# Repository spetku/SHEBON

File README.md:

# open_SHEBON
a platform for sensing and indicating bio-data!

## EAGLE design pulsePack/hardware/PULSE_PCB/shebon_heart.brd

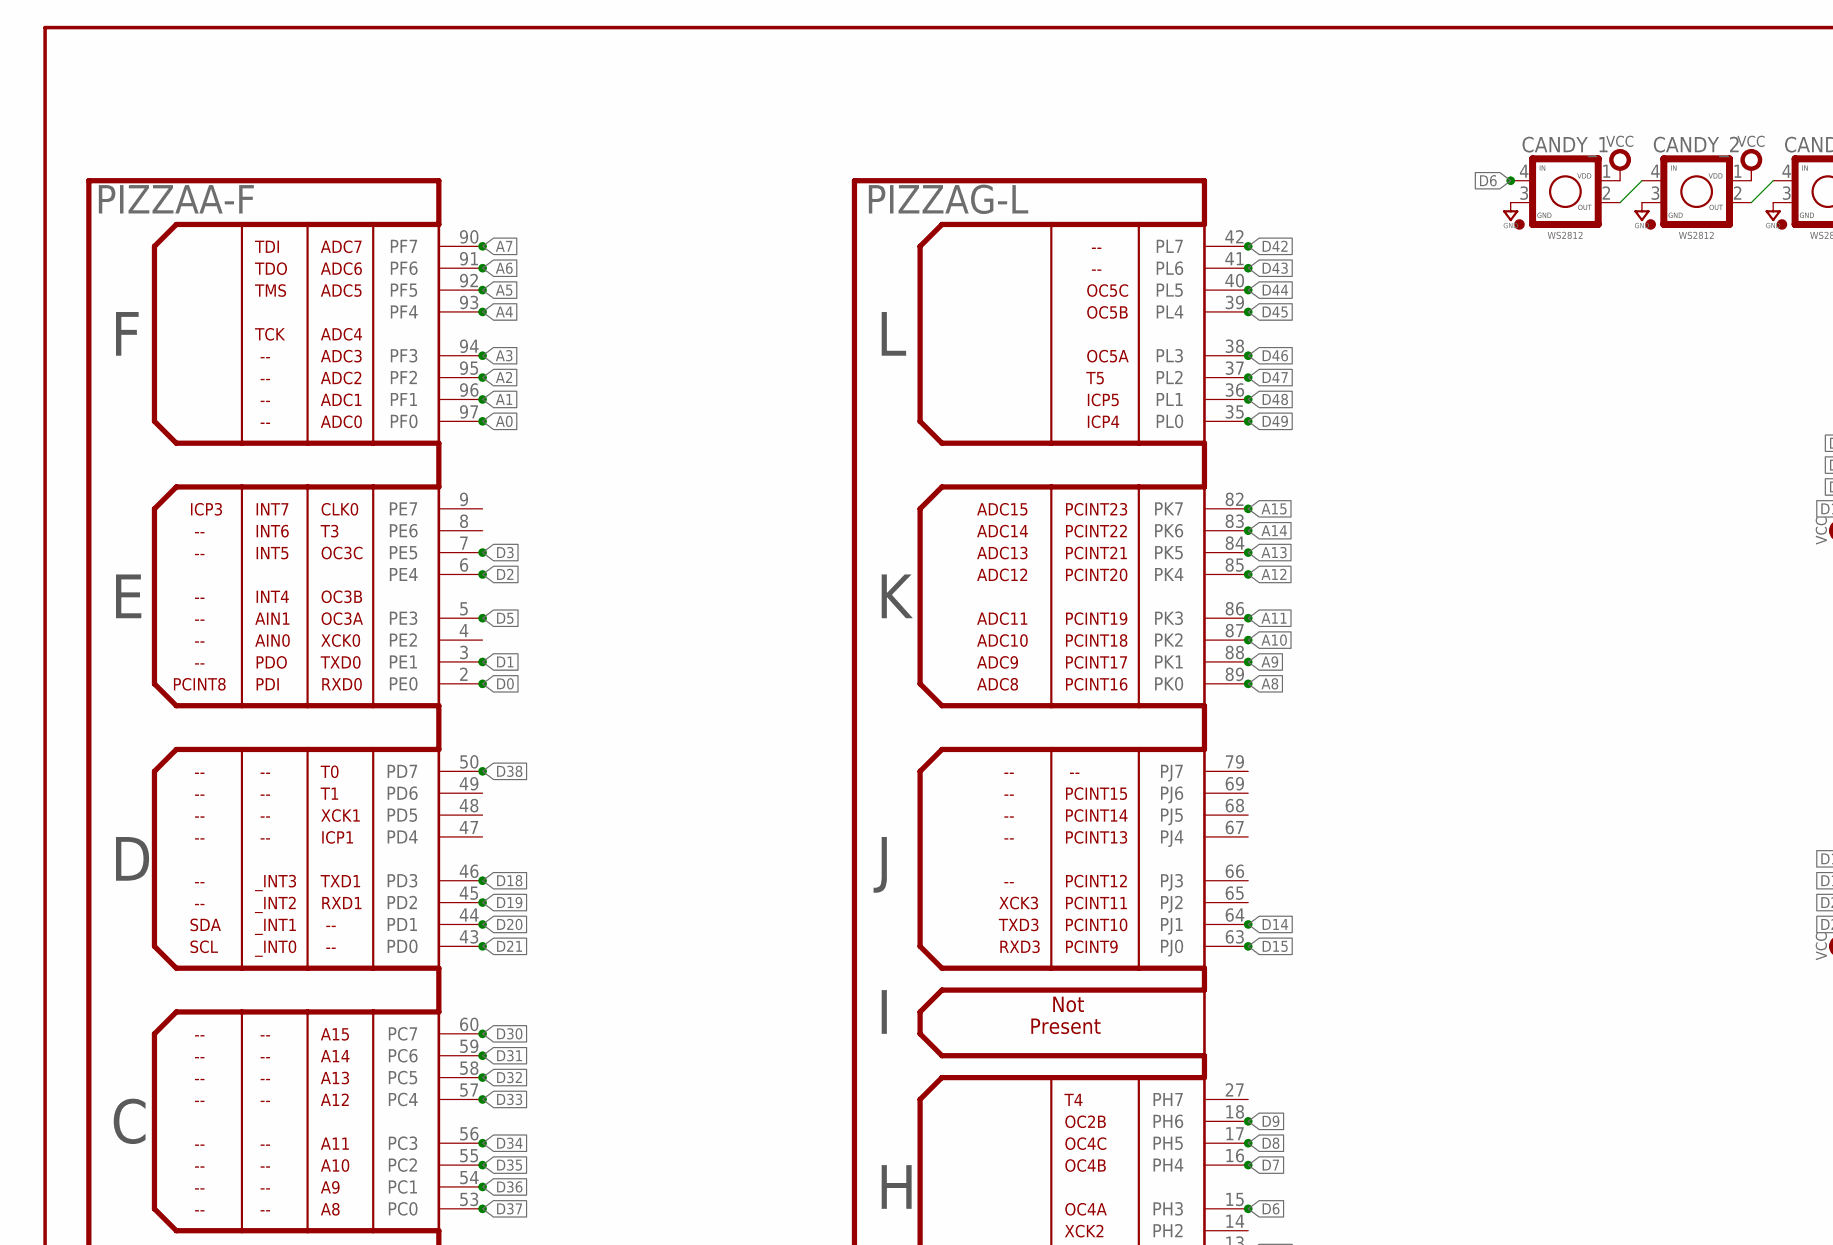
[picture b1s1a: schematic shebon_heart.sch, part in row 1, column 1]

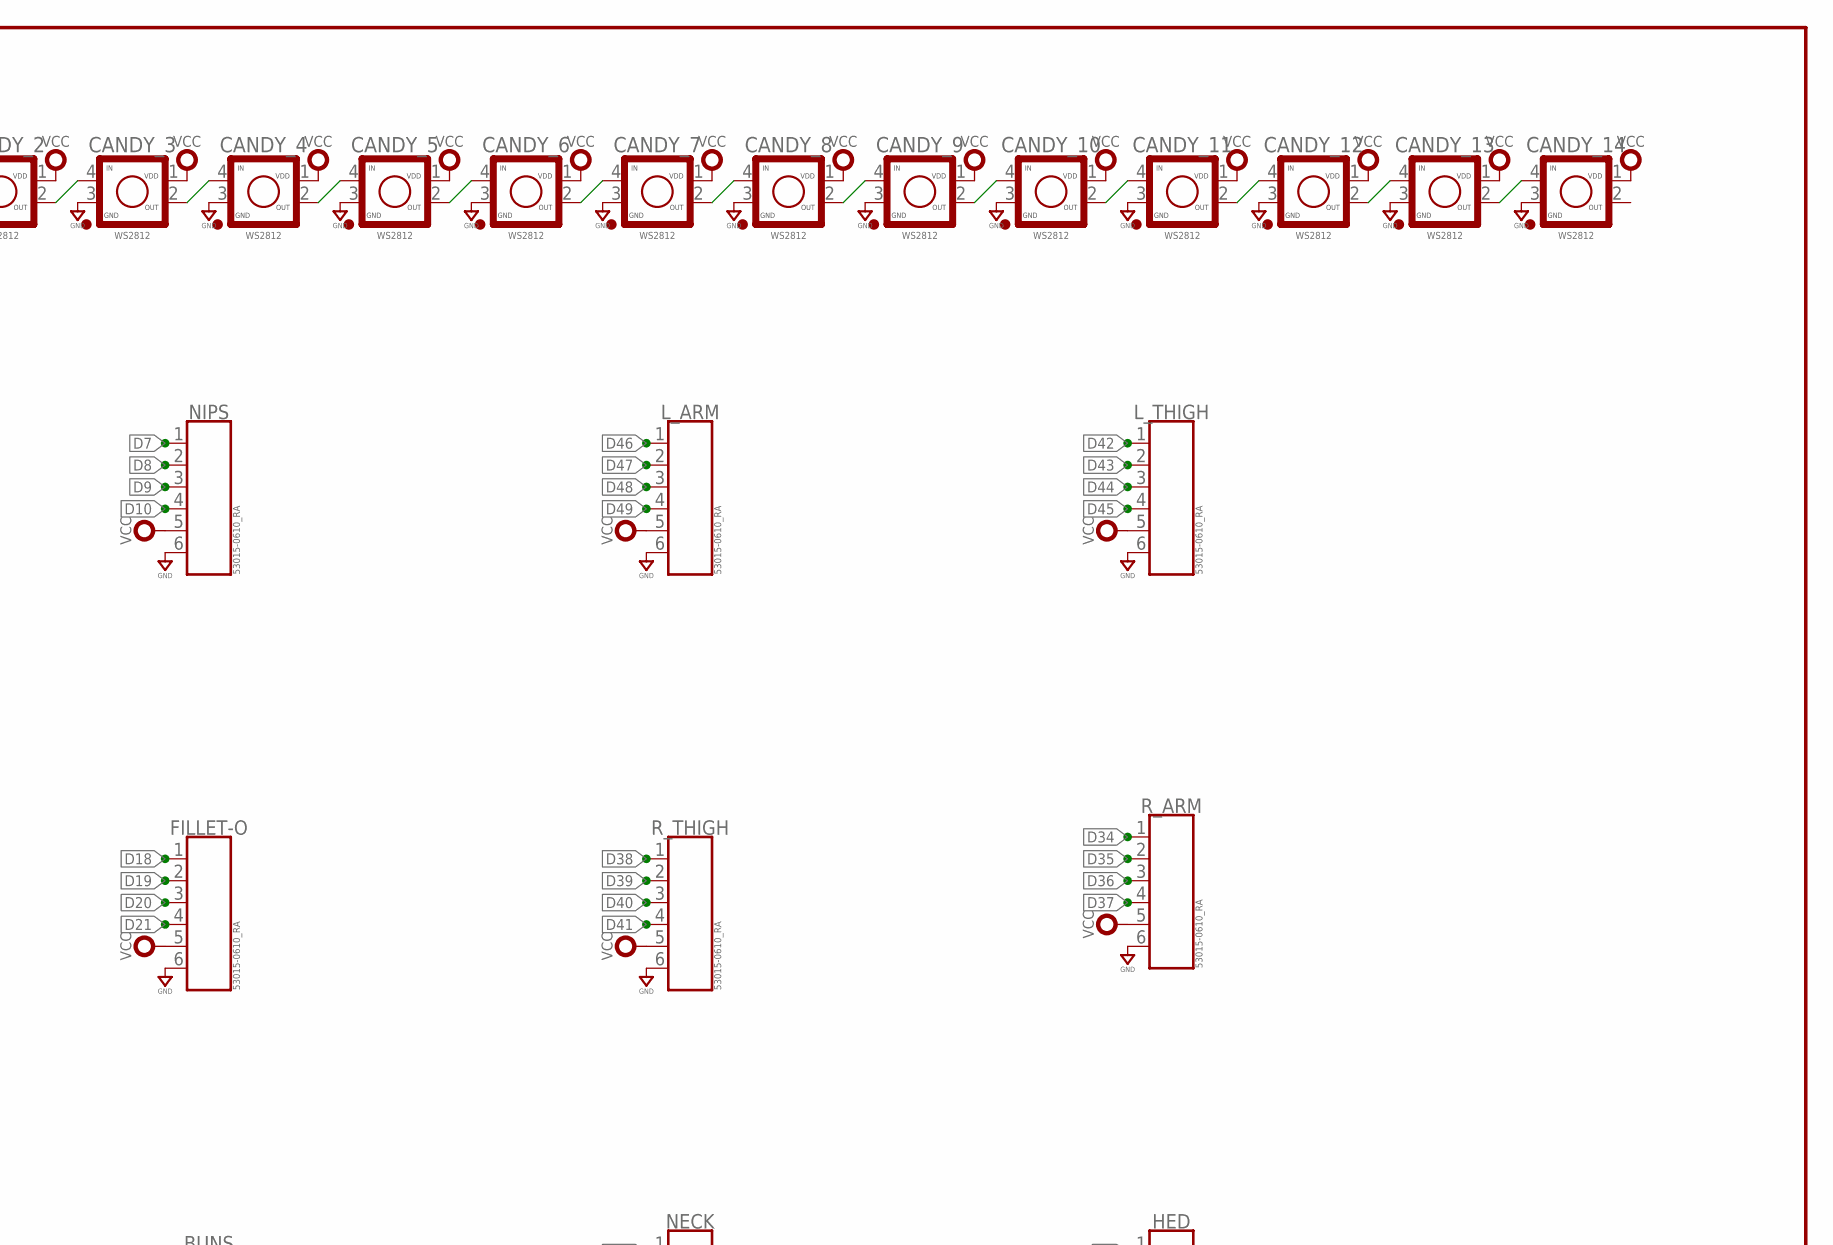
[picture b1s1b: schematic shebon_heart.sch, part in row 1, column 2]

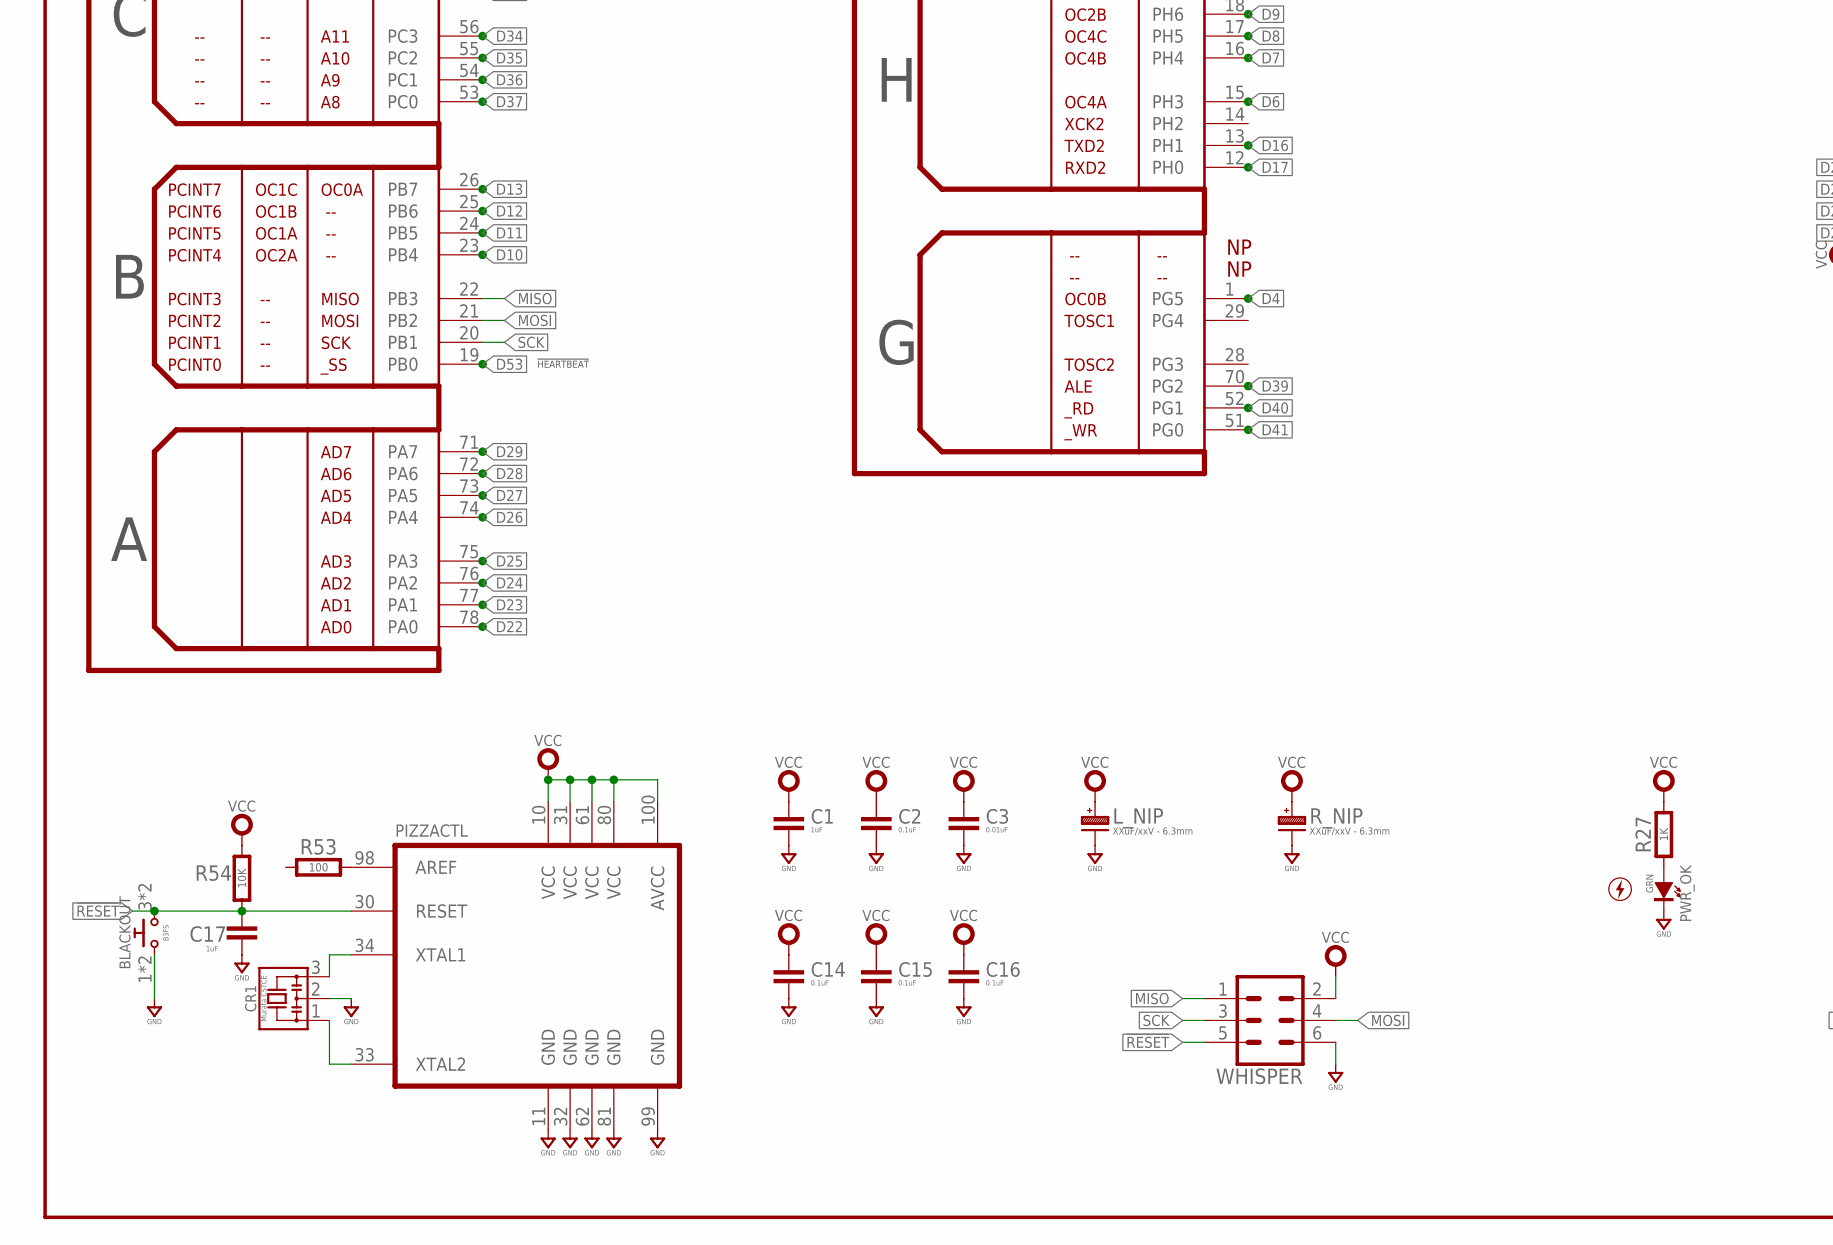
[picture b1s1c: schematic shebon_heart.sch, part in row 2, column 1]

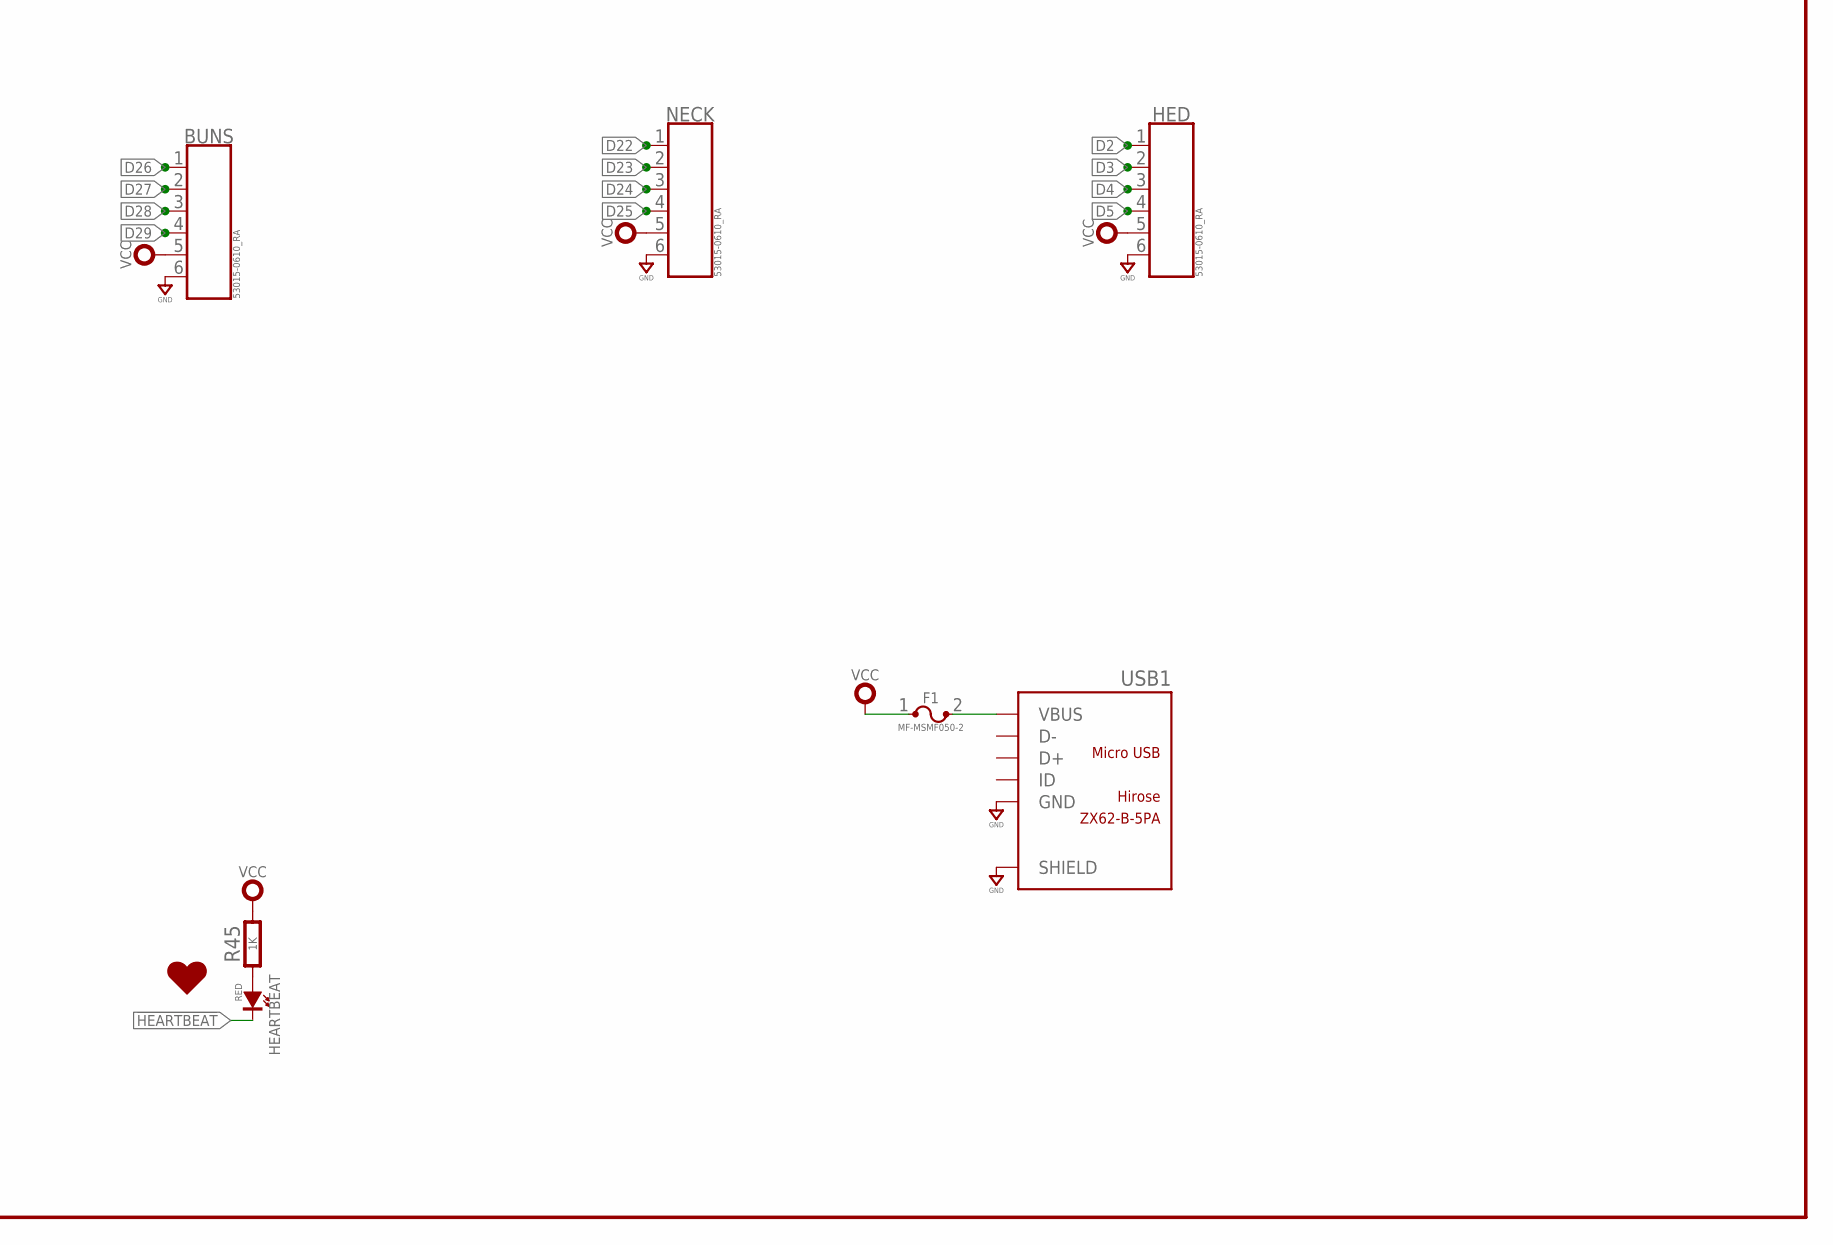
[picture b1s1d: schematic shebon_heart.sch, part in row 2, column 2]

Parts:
BLACKOUT: B3FS
BUNS: 53015-0610_RA; MICROBLADE-RA-06P
C1, C17: 1uF; 0603
C2, C14, C15, C16: 0.1uF; 0603
C3: 0.01uF; 0603
CANDY_1, CANDY_2, CANDY_3, CANDY_4, CANDY_5, CANDY_6, CANDY_7, CANDY_8, CANDY_9, CANDY_10, CANDY_11, CANDY_12, CANDY_13, CANDY_14: WS2812; NEOPIXEL
CR1: Murata CSTCE; MURATA_CSTCE
F1: MF-MSMF050-2; BOURNS-MF-MSMF
FILLET-O: 53015-0610_RA; MICROBLADE-RA-06P
HEARTBEAT: RED; SMD_0603
HED: 53015-0610_RA; MICROBLADE-RA-06P
L_ARM: 53015-0610_RA; MICROBLADE-RA-06P
L_NIP: XXuF/xxV - 6.3mm; CAP_ALUM_SMT_6.3
L_THIGH: 53015-0610_RA; MICROBLADE-RA-06P
NECK: 53015-0610_RA; MICROBLADE-RA-06P
NIPS: 53015-0610_RA; MICROBLADE-RA-06P
PIZZA: ATMEGA-2560; TQFP-100-A
PWR_OK: GRN; SMD_0603
R27, R45: 1K; 0603
R53: 100; 0603
R54: 10K; 0603
R_ARM: 53015-0610_RA; MICROBLADE-RA-06P
R_NIP: XXuF/xxV - 6.3mm; CAP_ALUM_SMT_6.3
R_THIGH: 53015-0610_RA; MICROBLADE-RA-06P
U$2: ELECTRICITY-050X050MM; ELECTRICITY-GLYPH-05X05MM
U$3: HEART-05X04MM; HEART-GLYPH-05X04MM
USB1: ZX62-B-5PA; MICRO-USB5+6P-SMD-0.65-AB
WHISPER: MA03-2

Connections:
!HEARTBEAT: HEARTBEAT.K (C)
!RESET: BLACKOUT.3 (2), BLACKOUT.4 (2), C17.1, PIZZA.30 (RESET), R54.2, WHISPER.5
A0: PIZZA.97 (PF0)
A1: PIZZA.96 (PF1)
A2: PIZZA.95 (PF2)
A3: PIZZA.94 (PF3)
A4: PIZZA.93 (PF4)
A5: PIZZA.92 (PF5)
A6: PIZZA.91 (PF6)
A7: PIZZA.90 (PF7)
A8: PIZZA.89 (PK0)
A9: PIZZA.88 (PK1)
A10: PIZZA.87 (PK2)
A11: PIZZA.86 (PK3)
A12: PIZZA.85 (PK4)
A13: PIZZA.84 (PK5)
A14: PIZZA.83 (PK6)
A15: PIZZA.82 (PK7)
D0: PIZZA.2 (PE0)
D1: PIZZA.3 (PE1)
D2: HED.1, PIZZA.6 (PE4)
D3: HED.2, PIZZA.7 (PE5)
D4: HED.3, PIZZA.1 (PG5)
D5: HED.4, PIZZA.5 (PE3)
D6: CANDY_1.4 (OUT), PIZZA.15 (PH3)
D7: NIPS.1, PIZZA.16 (PH4)
D8: NIPS.2, PIZZA.17 (PH5)
D9: NIPS.3, PIZZA.18 (PH6)
D10: NIPS.4, PIZZA.23 (PB4)
D11: PIZZA.24 (PB5)
D12: PIZZA.25 (PB6)
D13: PIZZA.26 (PB7)
D14: PIZZA.64 (PJ1)
D15: PIZZA.63 (PJ0)
D16: PIZZA.13 (PH1)
D17: PIZZA.12 (PH0)
D18: FILLET-O.1, PIZZA.46 (PD3)
D19: FILLET-O.2, PIZZA.45 (PD2)
D20: FILLET-O.3, PIZZA.44 (PD1)
D21: FILLET-O.4, PIZZA.43 (PD0)
D22: NECK.1, PIZZA.78 (PA0)
D23: NECK.2, PIZZA.77 (PA1)
D24: NECK.3, PIZZA.76 (PA2)
D25: NECK.4, PIZZA.75 (PA3)
D26: BUNS.1, PIZZA.74 (PA4)
D27: BUNS.2, PIZZA.73 (PA5)
D28: BUNS.3, PIZZA.72 (PA6)
D29: BUNS.4, PIZZA.71 (PA7)
D30: PIZZA.60 (PC7)
D31: PIZZA.59 (PC6)
D32: PIZZA.58 (PC5)
D33: PIZZA.57 (PC4)
D34: PIZZA.56 (PC3), R_ARM.1
D35: PIZZA.55 (PC2), R_ARM.2
D36: PIZZA.54 (PC1), R_ARM.3
D37: PIZZA.53 (PC0), R_ARM.4
D38: PIZZA.50 (PD7), R_THIGH.1
D39: PIZZA.70 (PG2), R_THIGH.2
D40: PIZZA.52 (PG1), R_THIGH.3
D41: PIZZA.51 (PG0), R_THIGH.4
D42: L_THIGH.1, PIZZA.42 (PL7)
D43: L_THIGH.2, PIZZA.41 (PL6)
D44: L_THIGH.3, PIZZA.40 (PL5)
D45: L_THIGH.4, PIZZA.39 (PL4)
D46: L_ARM.1, PIZZA.38 (PL3)
D47: L_ARM.2, PIZZA.37 (PL2)
D48: L_ARM.3, PIZZA.36 (PL1)
D49: L_ARM.4, PIZZA.35 (PL0)
D53: PIZZA.19 (PB0)
GND: BLACKOUT.1, BLACKOUT.2 (1), BUNS.6, C1.2, C2.2, C3.2, C14.2, C15.2, C16.2, C17.2, CANDY_1.3 (GND), CANDY_2.3 (GND), CANDY_3.3 (GND), CANDY_4.3 (GND), CANDY_5.3 (GND), CANDY_6.3 (GND), CANDY_7.3 (GND), CANDY_8.3 (GND), CANDY_9.3 (GND), CANDY_10.3 (GND), CANDY_11.3 (GND), CANDY_12.3 (GND), CANDY_13.3 (GND), CANDY_14.3 (GND), CR1.2, FILLET-O.6, HED.6, L_ARM.6, L_NIP.- (N), L_THIGH.6, NECK.6, NIPS.6, PIZZA.11 (GND), PIZZA.32 (GND), PIZZA.62 (GND), PIZZA.81 (GND), PIZZA.99 (GND), PWR_OK.K (C), R_ARM.6, R_NIP.- (N), R_THIGH.6, USB1.5 (GND), USB1.P1 (SHIELD), USB1.P2 (SHIELD), USB1.P3_1 (SHIELD), USB1.P3_2 (SHIELD), USB1.P3_3 (SHIELD), USB1.P4_1 (SHIELD), USB1.P4_2 (SHIELD), USB1.P4_3 (SHIELD), USB1.P5 (SHIELD), USB1.P6 (SHIELD), WHISPER.6
MISO: PIZZA.22 (PB3), WHISPER.1
MOSI: PIZZA.21 (PB2), WHISPER.4
unnamed: CR1.3, PIZZA.34 (XTAL1)
unnamed: CR1.1, PIZZA.33 (XTAL2)
unnamed: CANDY_1.2 (IN), CANDY_2.4 (OUT)
unnamed: CANDY_2.2 (IN), CANDY_3.4 (OUT)
unnamed: CANDY_3.2 (IN), CANDY_4.4 (OUT)
unnamed: CANDY_4.2 (IN), CANDY_5.4 (OUT)
unnamed: CANDY_5.2 (IN), CANDY_6.4 (OUT)
unnamed: CANDY_6.2 (IN), CANDY_7.4 (OUT)
unnamed: CANDY_7.2 (IN), CANDY_8.4 (OUT)
unnamed: CANDY_8.2 (IN), CANDY_9.4 (OUT)
unnamed: CANDY_9.2 (IN), CANDY_10.4 (OUT)
unnamed: CANDY_10.2 (IN), CANDY_11.4 (OUT)
unnamed: CANDY_11.2 (IN), CANDY_12.4 (OUT)
unnamed: CANDY_12.2 (IN), CANDY_13.4 (OUT)
unnamed: CANDY_13.2 (IN), CANDY_14.4 (OUT)
unnamed: PWR_OK.A, R27.1
unnamed: HEARTBEAT.A, R45.1
unnamed: PIZZA.98 (AREF), R53.2
SCK: PIZZA.20 (PB1), WHISPER.3
VBUS: F1.2, USB1.1 (VBUS)
VCC: BUNS.5, C1.1, C2.1, C3.1, C14.1, C15.1, C16.1, CANDY_1.1 (VDD), CANDY_2.1 (VDD), CANDY_3.1 (VDD), CANDY_4.1 (VDD), CANDY_5.1 (VDD), CANDY_6.1 (VDD), CANDY_7.1 (VDD), CANDY_8.1 (VDD), CANDY_9.1 (VDD), CANDY_10.1 (VDD), CANDY_11.1 (VDD), CANDY_12.1 (VDD), CANDY_13.1 (VDD), CANDY_14.1 (VDD), F1.1, FILLET-O.5, HED.5, L_ARM.5, L_NIP.+, L_THIGH.5, NECK.5, NIPS.5, PIZZA.10 (VCC), PIZZA.31 (VCC), PIZZA.61 (VCC), PIZZA.80 (VCC), PIZZA.100 (AVCC), R27.2, R45.2, R54.1, R_ARM.5, R_NIP.+, R_THIGH.5, WHISPER.2

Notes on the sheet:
!HEARTBEAT

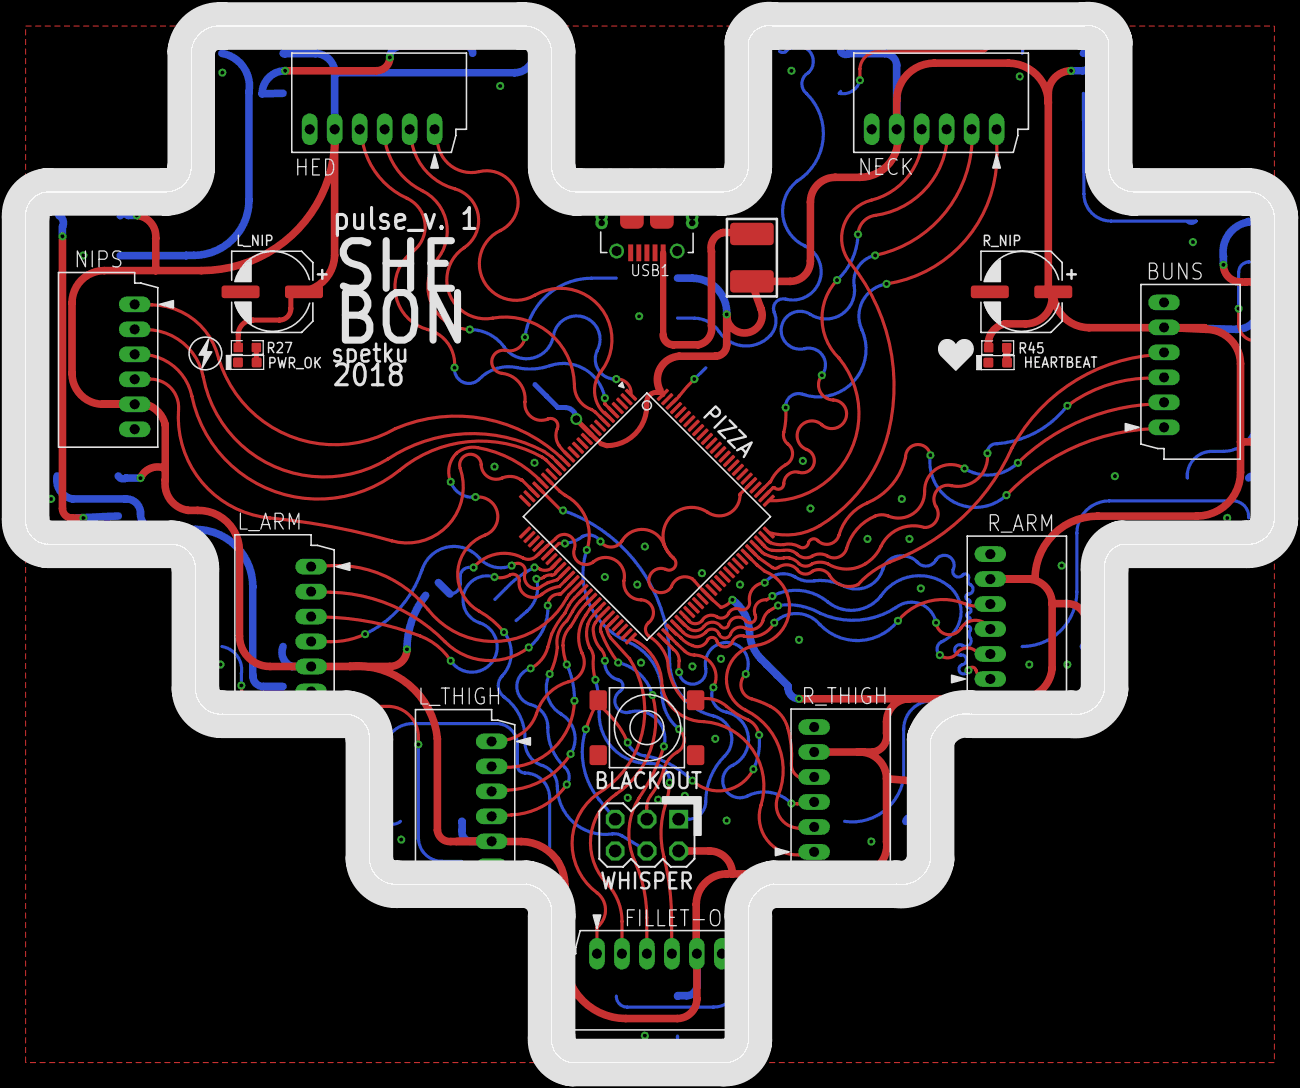
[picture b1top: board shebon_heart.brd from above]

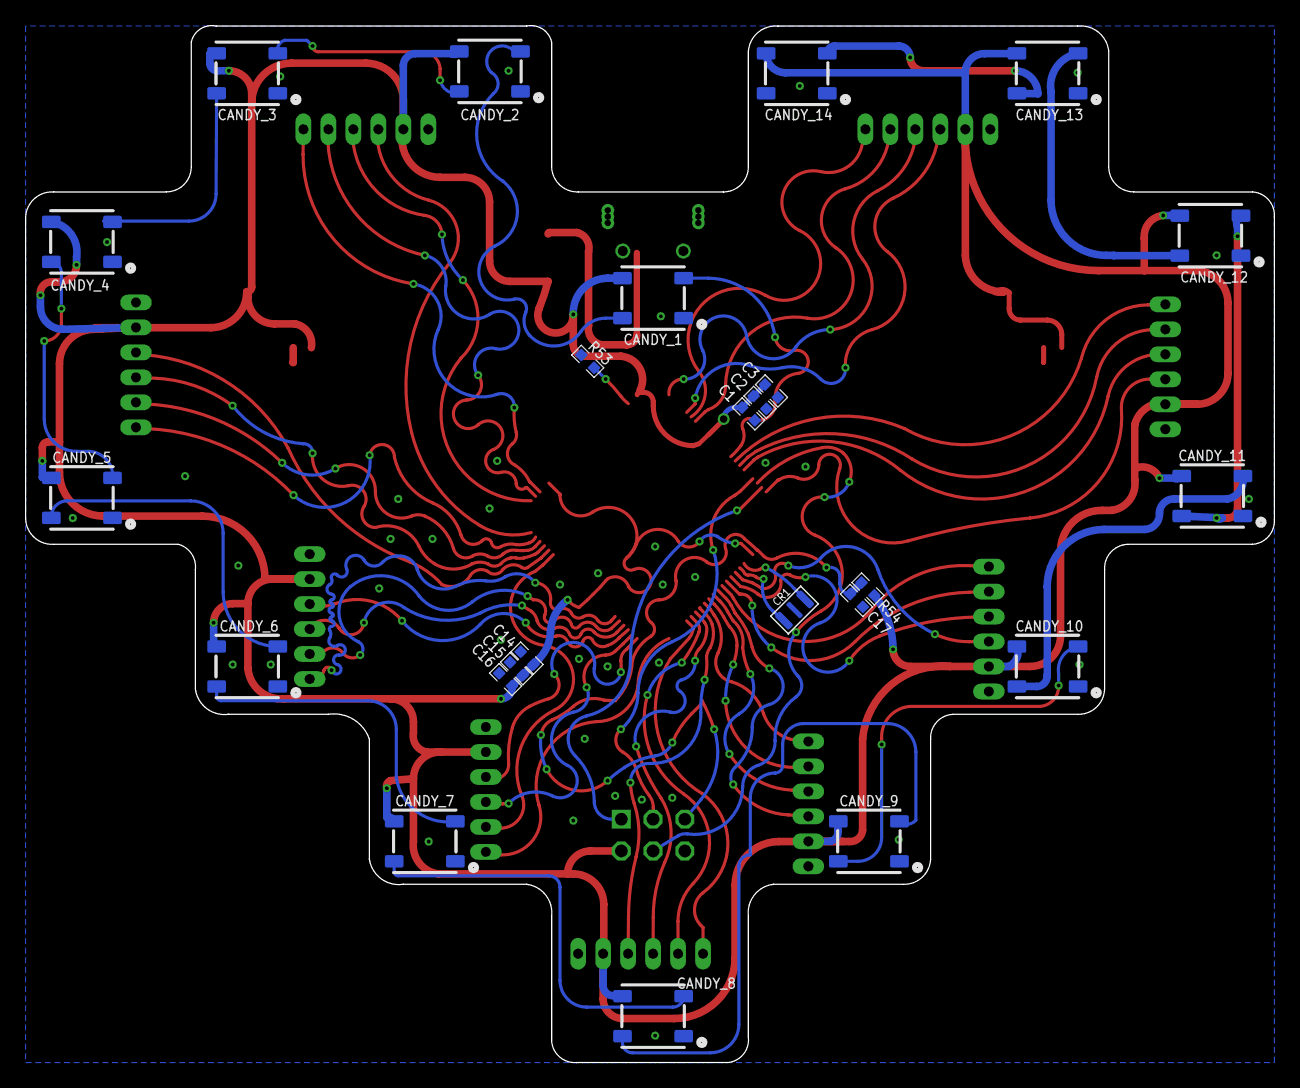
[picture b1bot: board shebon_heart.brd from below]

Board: 2 copper layers, 100.0 x 83.0 mm, 46 parts (24 on the bottom side), 62 nets.

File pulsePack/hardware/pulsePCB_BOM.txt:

SHE BON : PULSE | by SARAH PETKUS

Partlist exported from shebon_heart.sch at 10/21/18 2:06 PM

Part      Value                 Device                     Package                   Description                MPN        VALUE           
PIZZA                           ATMEGA-2560                TQFP-100-A                Atmel ATmega 640/1280/2560                            
BLACKOUT  B3FS                  PUSHBTN-MOMB3FS            B3FS                      Pushbutton Switch                     B3FS                      
C1        1uF                   CAPACITOR0603              0603                      Capacitor  CAP                                        
C2        0.1uF                 CAPACITOR0603              0603                      Capacitor  CAP                                        
C3        0.01uF                CAPACITOR0603              0603                      Capacitor  CAP                                        
C14       0.1uF                 CAPACITOR0603              0603                      Capacitor  CAP                                        
C15       0.1uF                 CAPACITOR0603              0603                      Capacitor  CAP                                        
C16       0.1uF                 CAPACITOR0603              0603                      Capacitor  CAP                                        
C17       1uF                   CAPACITOR0603              0603                      Capacitor  CAP                                        
L_NIP     330uF/6.3V - 6.3mm    CAPACITOR_POL-ALUM-SMT-6.3 CAP_ALUM_SMT_6.3          Polarized Capacitor                   XXuF/xxV - 6.3mm
R_NIP     330uF/6.3V - 6.3mm    CAPACITOR_POL-ALUM-SMT-6.3 CAP_ALUM_SMT_6.3          Polarized Capacitor                   XXuF/xxV - 6.3mm
CANDY_1   WS2812                NEOPPIXEL5X5               NEOPIXEL                  Adafruit NeoPixel                     WS2812          
CANDY_2   WS2812                NEOPPIXEL5X5               NEOPIXEL                  Adafruit NeoPixel                     WS2812          
CANDY_3   WS2812                NEOPPIXEL5X5               NEOPIXEL                  Adafruit NeoPixel                     WS2812          
CANDY_4   WS2812                NEOPPIXEL5X5               NEOPIXEL                  Adafruit NeoPixel                     WS2812          
CANDY_5   WS2812                NEOPPIXEL5X5               NEOPIXEL                  Adafruit NeoPixel                     WS2812          
CANDY_6   WS2812                NEOPPIXEL5X5               NEOPIXEL                  Adafruit NeoPixel                     WS2812          
CANDY_7   WS2812                NEOPPIXEL5X5               NEOPIXEL                  Adafruit NeoPixel                     WS2812          
CANDY_8   WS2812                NEOPPIXEL5X5               NEOPIXEL                  Adafruit NeoPixel                     WS2812          
CANDY_9   WS2812                NEOPPIXEL5X5               NEOPIXEL                  Adafruit NeoPixel                     WS2812          
CANDY_10  WS2812                NEOPPIXEL5X5               NEOPIXEL                  Adafruit NeoPixel                     WS2812          
CANDY_11  WS2812                NEOPPIXEL5X5               NEOPIXEL                  Adafruit NeoPixel                     WS2812          
CANDY_12  WS2812                NEOPPIXEL5X5               NEOPIXEL                  Adafruit NeoPixel                     WS2812          
CANDY_13  WS2812                NEOPPIXEL5X5               NEOPIXEL                  Adafruit NeoPixel                     WS2812          
CANDY_14  WS2812                NEOPPIXEL5X5               NEOPIXEL                  Adafruit NeoPixel                     WS2812          
CR1       Murata CSTCE          RESONATORMURATA-CSTCE      MURATA_CSTCE              resonator xtal                        Murata CSTCE    
F1        MF-MSMF050-2          FUSEBOURNS-MF-MSMF         BOURNS-MF-MSMF            Fuse                                  MF-MSMF050-2    
FILLET-O  53015-0610_RA         53015-0610_RA              MICROBLADE-RA-06P         Molex, Microblade, 6-pin                              
HED       53015-0610_RA         53015-0610_RA              MICROBLADE-RA-06P         Molex, Microblade, 6-pin                              
BUNS      53015-0610_RA         53015-0610_RA              MICROBLADE-RA-06P         Molex, Microblade, 6-pin                    
L_ARM     53015-0610_RA         53015-0610_RA              MICROBLADE-RA-06P         Molex, Microblade, 6-pin                              
L_THIGH   53015-0610_RA         53015-0610_RA              MICROBLADE-RA-06P         Molex, Microblade, 6-pin                              
R_ARM     53015-0610_RA         53015-0610_RA              MICROBLADE-RA-06P         Molex, Microblade, 6-pin                              
R_THIGH   53015-0610_RA         53015-0610_RA              MICROBLADE-RA-06P         Molex, Microblade, 6-pin                                                                                  
NECK      53015-0610_RA         53015-0610_RA              MICROBLADE-RA-06P         Molex, Microblade, 6-pin                              
NIPS      53015-0610_RA         53015-0610_RA              MICROBLADE-RA-06P         Molex, Microblade, 6-pin                              
WHISPER                         MA03-2                     MA03-2                    PIN HEADER                                            
USB1      ZX62-B-5PA            MICRO-USB-SMD(ZX62-B-5PA)  MICRO-USB5+6P-SMD-0.65-AB 320010005                  ZX62-B-5PA ZX62-B-5PA      
PWR_OK    GRN                   SMT0603                    SMD_0603                  LED SMT 0603 0805 1206                                
HEARTBEAT RED                   SMT0603                    SMD_0603                  LED SMT 0603 0805 1206                                
R27       1K                    RESISTOR0603               0603                      Resistor                                              
R45       1K                    RESISTOR0603               0603                      Resistor                                              
R53       100                   RESISTOR0603               0603                      Resistor                                              
R54       10K                   RESISTOR0603               0603                      Resistor

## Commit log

2018-10-20 popGirl v.1 STL files added
    First version of the popGirl enclosure
2018-10-21 Ignore DS_Store files
    Ignore DS_store files
2018-10-21 folder name change
    I reorganized stuff
2018-10-21 No more DS_Store
    Remove all DS_Store files.
2018-10-21 Added Hardware Setup Notes
    Hardware setup notes.
2018-10-21 Added PCB
    Added PULSE and BOM
2018-10-21 Remove unwanted design and gerber crud.
2018-10-21 Move Gerber ZIP to higher dir.
2018-10-21 Added schematic PDF
2018-10-21 PopGirl Java app source added.
    PopGirl Java application source files and Netbeans project.
2018-10-21 Screen shot for Java config.
    Screen shot showing addition of external pi4j jar files needed in order to compile application from Netbeans.
2018-10-21 Upload screen shots
2018-10-21 Added screen shots.
2018-10-21 Revert "Added screen shots."
    This reverts commit e2c2ac344400e975e943978e154360930ed2dc12.
2018-10-21 Revert "Revert "Added screen shots.""
    This reverts commit 5074bdc09033deea68f16b91714d259e4263aa06.
2018-10-21 Revert "Upload screen shots"
    This reverts commit 2790f382113a5d70439801235230554f9393f134.
2018-10-21 Revert "Revert "Upload screen shots""
    This reverts commit ddb5b1acabd1123ac26ff97ccc6098e2182d7d28.
2018-10-21 screenshots wont upload
2018-10-21 Screen shot git upload fun!
2018-10-21 Revert "Screen shot git upload fun!"
    This reverts commit 30dad15305dc140c81ef2fc295578319b4019081.
2018-10-21 Update popGirl/software/screenshots
2018-10-21 Grab hair. Pull. Repeat.
2018-10-22 Screenshots
2018-10-26 Fix broken screenshot image link
2018-10-26 Pulse Pack Firmware v1
2019-03-16 Stuff
2019-03-17 bra working with two motors and sensors
